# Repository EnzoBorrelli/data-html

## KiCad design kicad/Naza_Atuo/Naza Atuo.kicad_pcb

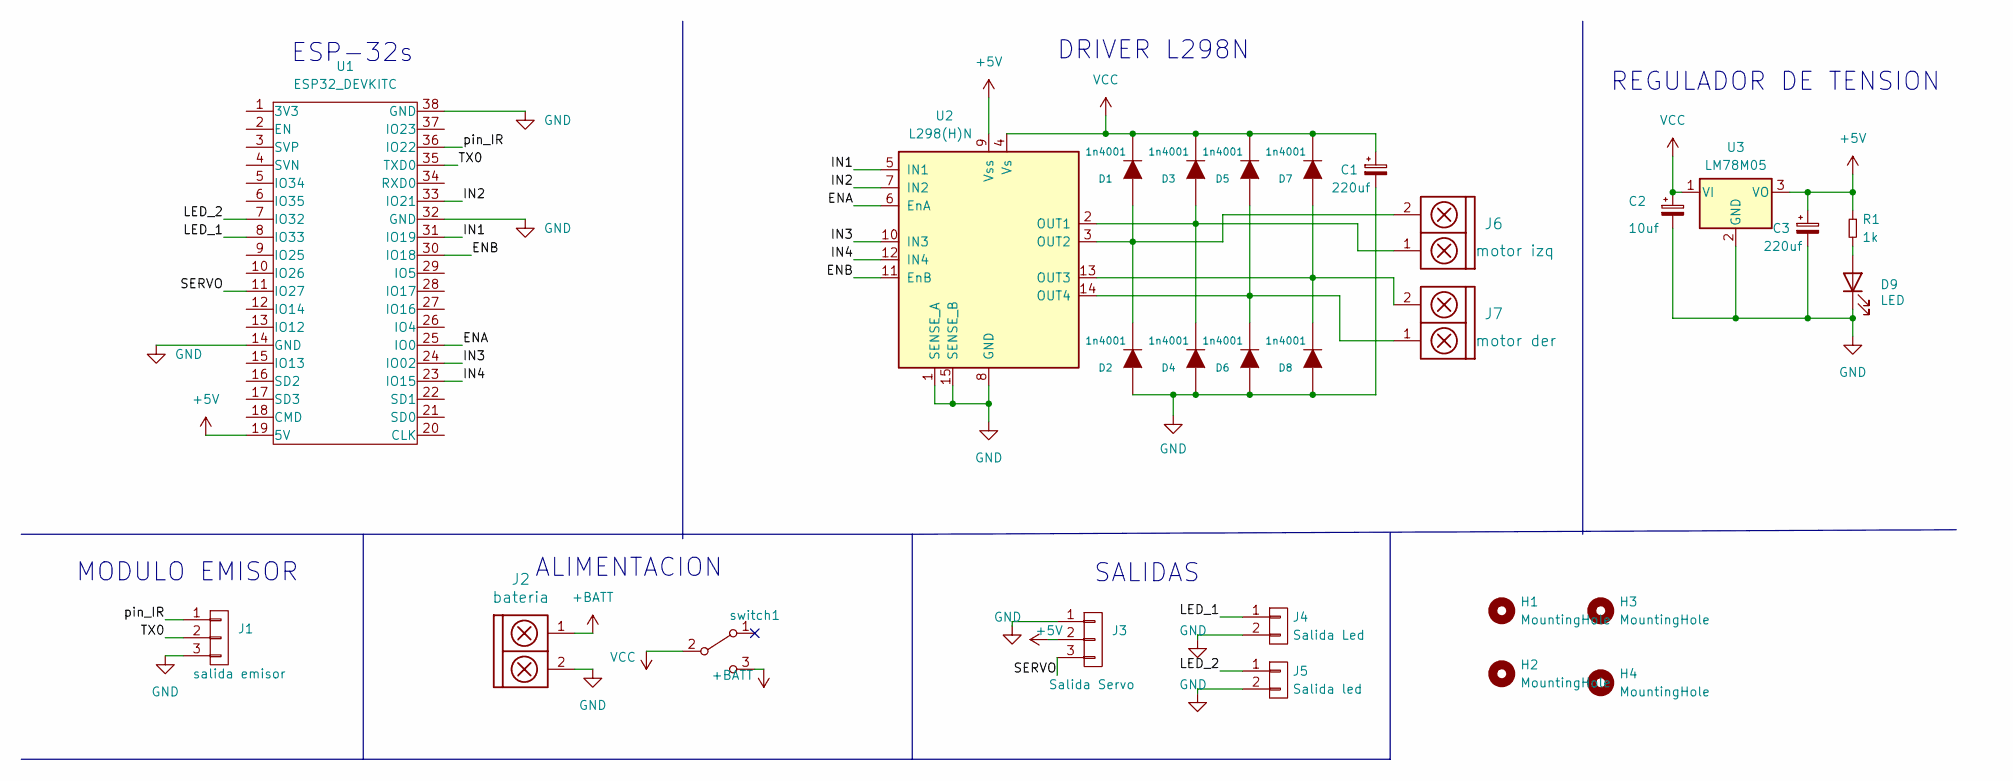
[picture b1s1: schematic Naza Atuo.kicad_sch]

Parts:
C1, C3: 220uf; CP_Radial_D5.0mm_P2.00mm
C2: 10uf; CP_Radial_D5.0mm_P2.00mm
D1, D2, D3, D4, D5, D6, D7, D8: 1n4001; DO-41
D9: LED; led_3mm_clear
H1, H2, H3, H4: MountingHole; MountingHole_3mm
J1: salida emisor; JST_EH_B3B-EH-A_1x03_P2.50mm_Vertical
J2: bateria; BORNERA2_AZUL
J3: Salida Servo; JST_EH_B3B-EH-A_1x03_P2.50mm_Vertical
J4: Salida Led; JST_EH_B2B-EH-A_1x02_P2.50mm_Vertical
J5: Salida led; JST_EH_B2B-EH-A_1x02_P2.50mm_Vertical
J6: motor izq; BORNERA2_AZUL
J7: motor der; BORNERA2_AZUL
R1: 1k; RES0.3
U1: ESP32_DEVKITC; ESP32S
U2: L298(H)N; TO-220-15_P2.54x2.54mm_StaggerEven_Lead4.58mm_Vertical
U3: LM78M05; TO-220-3_Vertical
switch1: SW_SPDT; SW_SPDT_TH_Vertical

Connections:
+5V: C3.1, J3.2, R1.1, U1.19 (5V), U2.9 (Vss), U3.3 (VO)
+BATT: J2.1, switch1.3 (C)
/ENA: U1.25 (IO0), U2.6 (EnA)
/ENB: U1.30 (IO18), U2.11 (EnB)
/IN1: U1.31 (IO19), U2.5 (IN1)
/IN2: U1.33 (IO21), U2.7 (IN2)
/IN3: U1.24 (IO02), U2.10 (IN3)
/IN4: U1.23 (IO15), U2.12 (IN4)
/LED_1: J4.1, U1.8 (IO33)
/LED_2: J5.1, U1.7 (IO32)
/SERVO: J3.3, U1.11 (IO27)
/TX0: J1.2, U1.35 (TXD0)
/pin_IR: J1.1, U1.36 (IO22)
GND: C1.2, C2.2, C3.2, D2.1 (A), D4.1 (A), D6.1 (A), D8.1 (A), D9.1 (K), J1.3, J2.2, J3.1, J4.2, J5.2, U1.14 (GND), U1.32 (GND), U1.38 (GND), U2.1 (SENSE_A), U2.8 (GND), U2.15 (SENSE_B), U3.2 (GND)
unnamed: D1.1 (A), D2.2 (K), J6.2, U2.3 (OUT2)
unnamed: D3.1 (A), D4.2 (K), J6.1, U2.2 (OUT1)
unnamed: D5.1 (A), D6.2 (K), J7.1, U2.14 (OUT4)
unnamed: D7.1 (A), D8.2 (K), J7.2, U2.13 (OUT3)
unnamed: D9.2 (A), R1.2
VCC: C1.1, C2.1, D1.2 (K), D3.2 (K), D5.2 (K), D7.2 (K), U2.4 (Vs), U3.1 (VI), switch1.2 (B)

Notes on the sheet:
ESP-32s
SALIDAS
ALIMENTACION
DRIVER L298N
REGULADOR DE TENSION
MODULO EMISOR

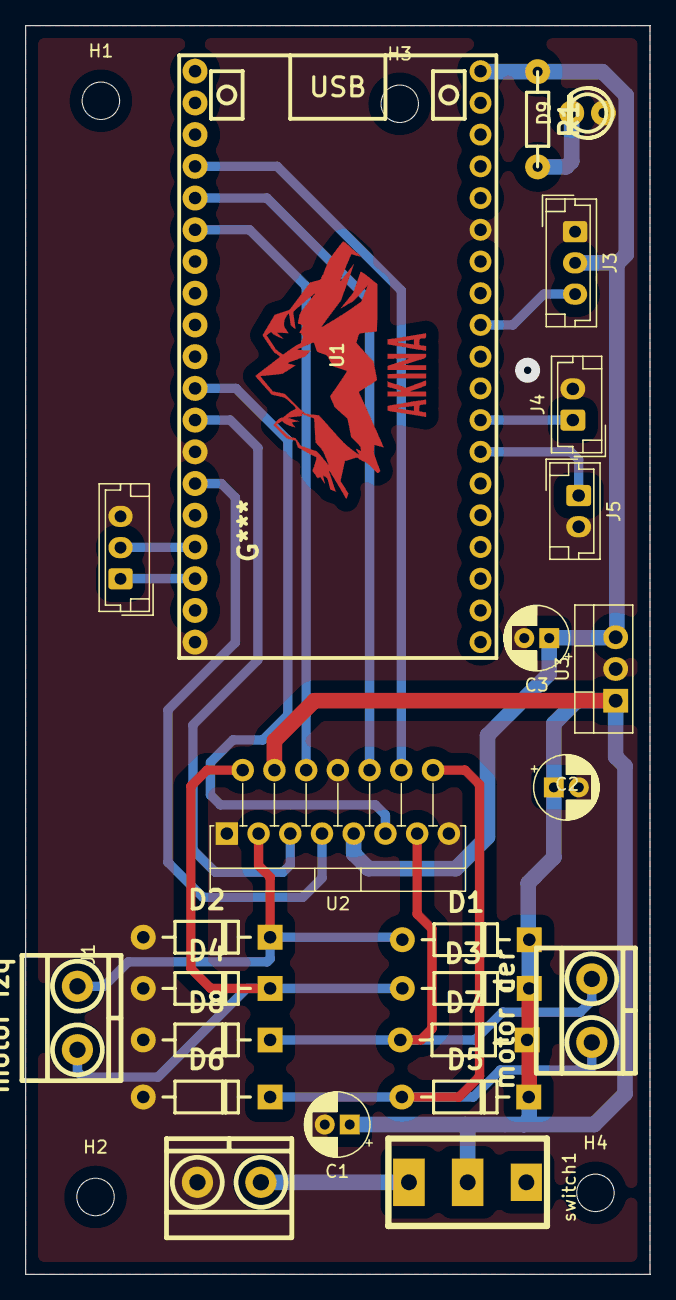
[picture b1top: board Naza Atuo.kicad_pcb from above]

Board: 2 copper layers, 50.0 x 100.0 mm, 28 parts (0 on the bottom side), 20 nets.

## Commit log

2022-11-25 repositorio para informe html
2022-11-28 fotos para html
2022-11-28 actualización de iamgenes
